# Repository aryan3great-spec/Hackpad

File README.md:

**i have taken inspiration and guidance from the guide provided by hack club;I intend to use it to setup macros for while I am writing notes to swtich colours**
**and whatnot; or for multimedia control ; or too play minecraft lol , thinking of speedrunning the game** 
**For simple functioning of the macropad i have decided on 4 buttons to execute tasks as mentioned above.**

PS: I apologise for the ugly formatting havent gotten down to learn how to use github quite yet 

**This will be the design of my hackpad** 

**This is the schematic**

**This is the PCB**

**BOM:**

- **Switches:** Cherry MX switches (x4)— ~₹450 ($5) — [[link](https://www.thecosmicbyte.com/product/cherry-mx-mechancial-5-pin-switches-compatible-with-hot-swappable-keyboards-pack-of-10/?attribute_pa_switch-type=mx-speed-silver&utm_source=Google%20Shopping&utm_campaign=googlefeeds&utm_medium=cpc&utm_term=78990&gad_source=1&gad_campaignid=19219700337&gclid=CjwKCAiAv5bMBhAIEiwAqP9GuCN7dUWZ0w-tPH6VcoadQNVbTonr9JJgzO3VEh77yX3e2vDeZ7oI5xoCWEkQAvD_BwE)]
- **LEDs:** SK6812 Mini-E — ~₹261 ($3) for 10 — [[link](https://www.digikey.in/en/products/detail/adafruit-industries-llc/4960/14302512)]
- **MCU:** Seeed XIAO RP2040 — ~₹618 ($8) — [[link](https://robu.in/product/seeed-studio-xiao-rp2040-v1-0/)]
- **Keycaps:** DSA Blank PBT — ~₹600 ($7) — [[link](https://amzn.in/d/00PxhO5Z)]
- **Bolts:** M3x16 — ~₹70 ($0.8) — [[link](https://robu.in/product/easymech-ss304-m3-x-16-mm-socket-head-cap-allen-bolt-25-pcs/?gad_source=1&gad_campaignid=20387462343&gclid=CjwKCAiAv5bMBhAIEiwAqP9GuAi0ALPmh37EGSJxq-MzcdSYqMAELKtpjN-rcK9-zXVzLzijvRrglRoCllkQAvD_BwE)]
- **Heat Inserts:** M3 Heat Sets — ~₹90 ($1.) — [[link](https://robu.in/product/easymech-ss304-m3-x-16-mm-socket-head-cap-allen-bolt-25-pcs/?gad_source=1&gad_campaignid=20387462343&gclid=CjwKCAiAv5bMBhAIEiwAqP9GuAi0ALPmh37EGSJxq-MzcdSYqMAELKtpjN-rcK9-zXVzLzijvRrglRoCllkQAvD_BwE)]

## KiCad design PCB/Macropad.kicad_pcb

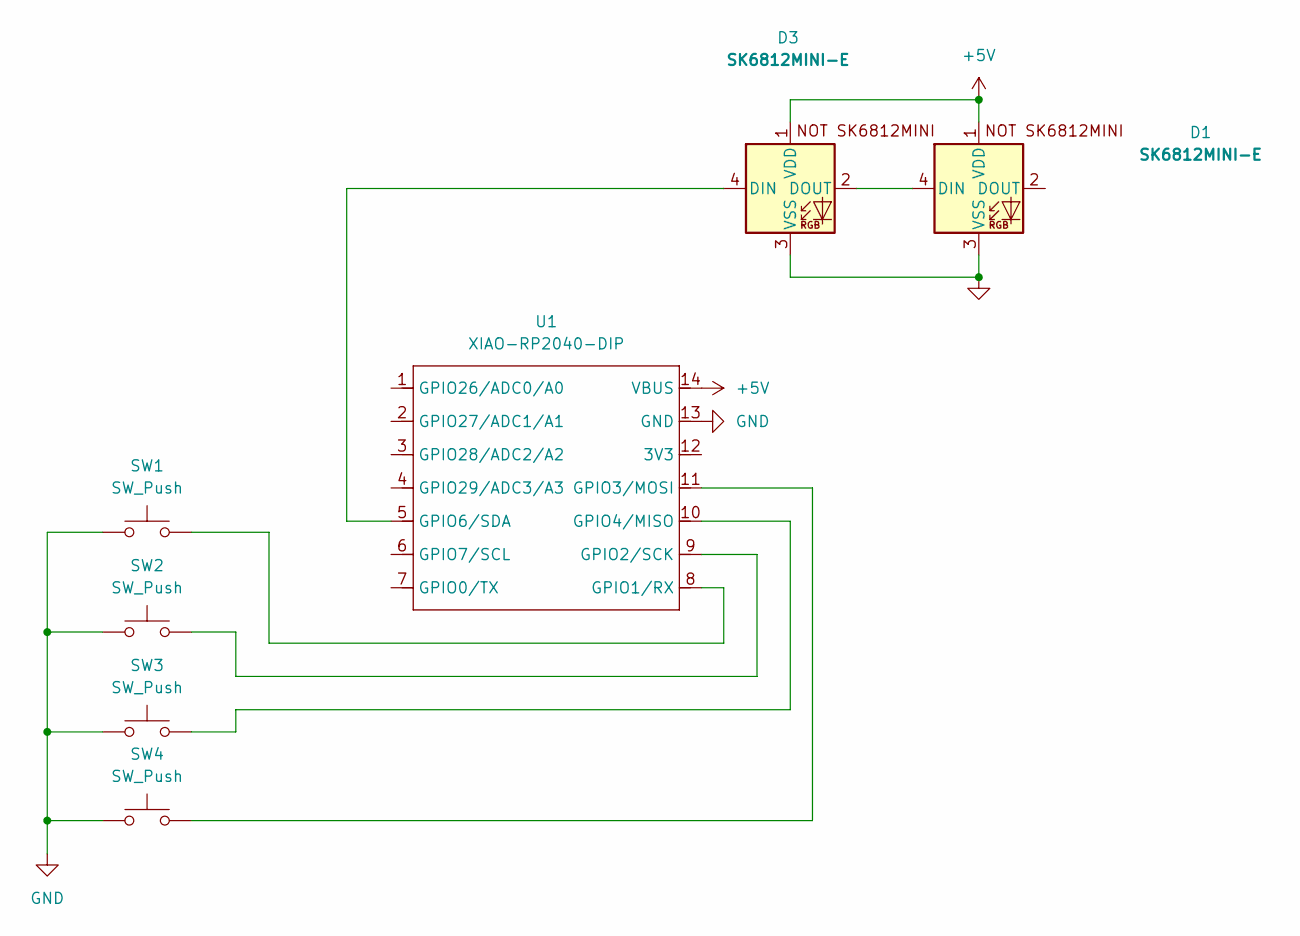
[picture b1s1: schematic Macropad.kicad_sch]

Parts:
D1, D3: SK6812MINI-E; MX_SK6812MINI-E_REV
SW1, SW2, SW3, SW4: SW_Push; SW_Cherry_MX_1.00u_PCB
U1: XIAO-RP2040-DIP

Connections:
+5V: D1.1 (VDD), D3.1 (VDD), U1.14 (VBUS)
GND: D1.3 (VSS), D3.3 (VSS), SW1.1, SW2.1, SW3.1, SW4.1, U1.13 (GND)
unnamed: D1.4 (DIN), D3.2 (DOUT)
unnamed: D3.4 (DIN), U1.5 (GPIO6/SDA)
unnamed: SW1.2, U1.8 (GPIO1/RX)
unnamed: SW2.2, U1.9 (GPIO2/SCK)
unnamed: SW4.2, U1.11 (GPIO3/MOSI)
unnamed: SW3.2, U1.10 (GPIO4/MISO)

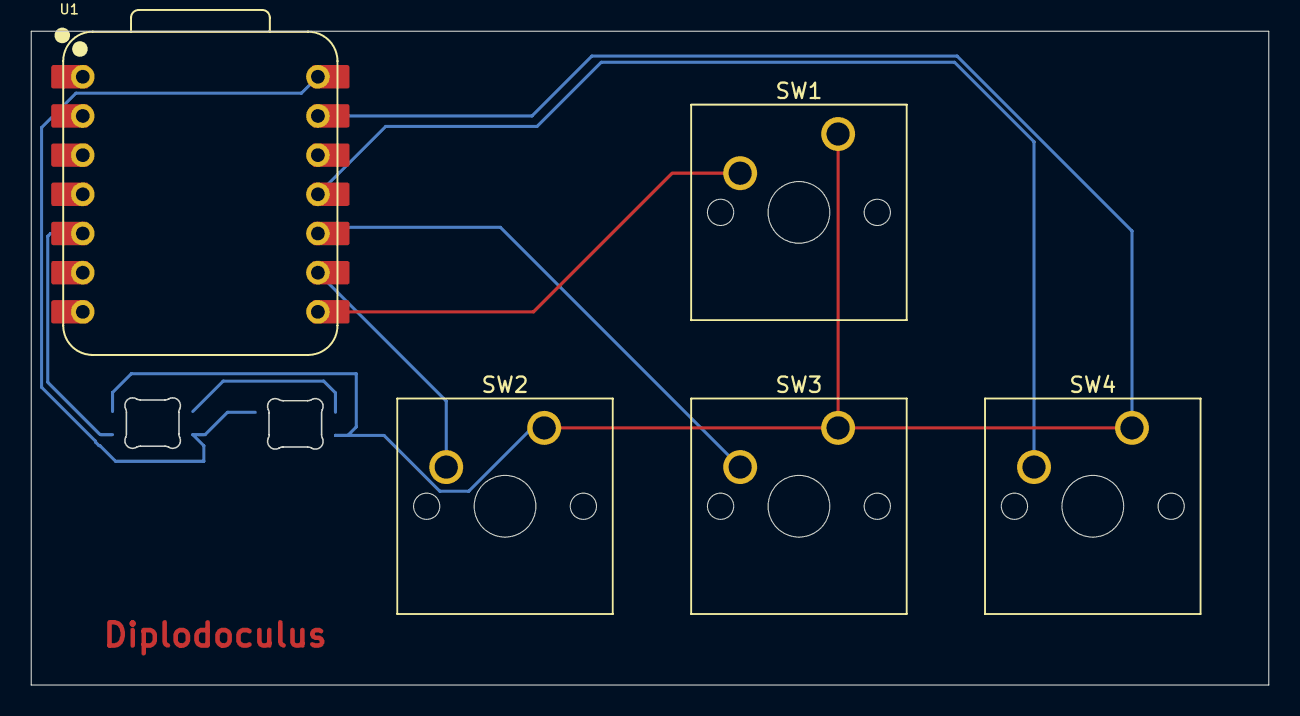
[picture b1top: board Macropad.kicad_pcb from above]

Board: 2 copper layers, 80.2 x 42.4 mm, 7 parts (0 on the bottom side), 8 nets.

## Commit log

2026-01-27 Initial hackpad commit
2026-01-27 Add images to README.md
2026-02-05 Revise BOM and add images to README
    Updated BOM to include new components and corrected LED type.
2026-02-05 Update PCB layout and schematic
2026-02-05 Add new images to README for schematic and PCB
    Added additional images for schematic and PCB sections.
2026-02-06 Update README with more images and BOM details
    Added additional images for schematic and PCB sections.
2026-02-06 Update README with hackpad design details
    Expanded on the purpose and functionality of the hackpad, including inspiration and intended uses.
2026-02-06 Improve README formatting and enhance BOM details
    Formatted the README for better readability and added links to BOM components.
